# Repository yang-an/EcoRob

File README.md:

# EcoRob

Hier entsteht ein Repo für das Projekt AT im Wintersemester 2017/18 an der Hochschule München.

## Wozu kann das Repo verwendet werden?
* Software-Entwicklung
* Kommunikation (z.B. Abwesenheiten)
* Dokumentation (Wiki)
* ...

## Weitere Inhalte folgen!

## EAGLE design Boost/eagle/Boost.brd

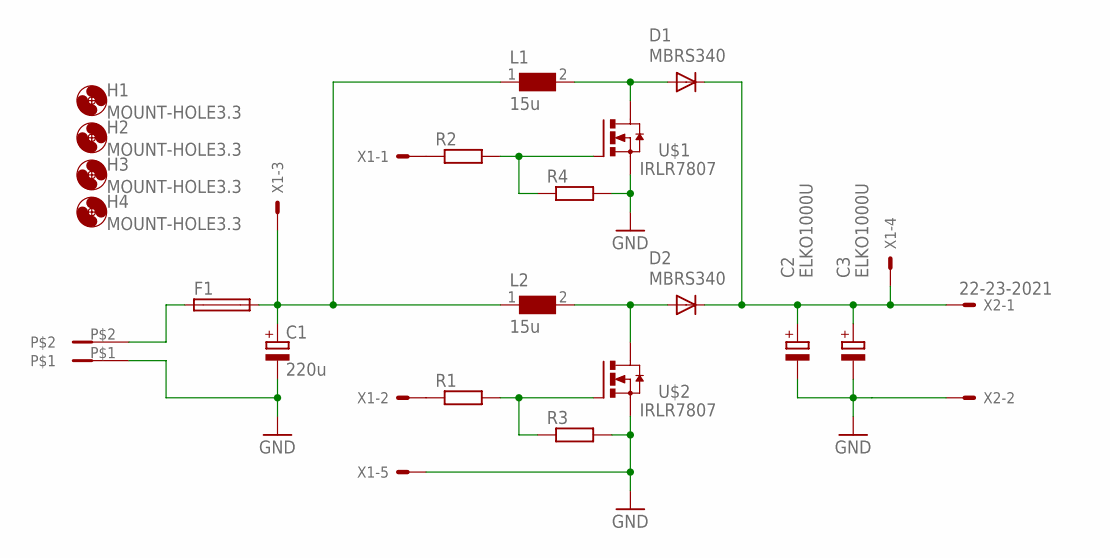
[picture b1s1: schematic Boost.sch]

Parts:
C1: 220u; PANASONIC_F
C2, C3: ELKO1000U; J16
D1, D2: MBRS340; SMC
F1: SH22,5
H1, H2, H3, H4: MOUNT-HOLE3.3; 3,3
L1, L2: 15u; WE-PD_1260/1245/1280/1210
R1, R2, R3, R4: R-EU_MELF0204W; MINI_MELF-0204W
U$1, U$2: IRLR7807; D-PAK
U$3: RIACON-2; RIACON2
X1: 22-23-2051
X2: 22-23-2021

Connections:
GND: C1.-, C2.-, C3.-, R3.2, R4.2, U$1.3 (S), U$2.3 (S), U$3.P$1, X1.5, X2.2
unnamed: F1.1, U$3.P$2
unnamed: R2.2, R4.1, U$1.1 (G)
unnamed: R1.1, X1.2
unnamed: R2.1, X1.1
unnamed: R1.2, R3.1, U$2.1 (G)
SW1: D1.A, L1.2, U$1.4 (D)
SW2: D2.A, L2.2, U$2.4 (D)
UIN: C1.+, F1.2, L1.1, L2.1, X1.3
UOUT: C2.+, C3.+, D1.C, D2.C, X1.4, X2.1

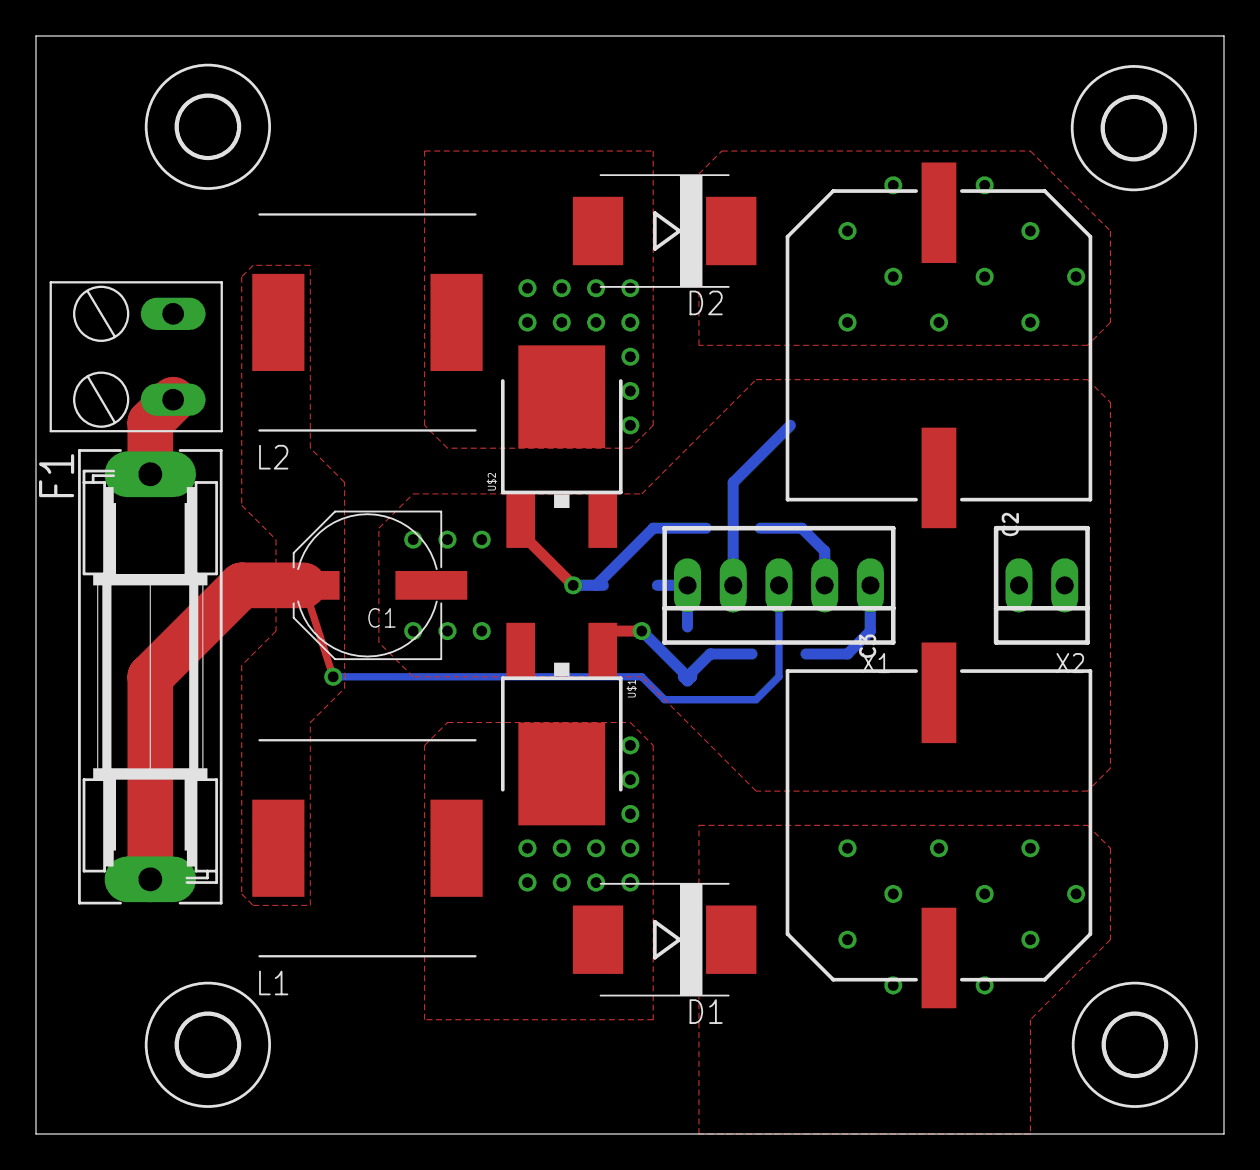
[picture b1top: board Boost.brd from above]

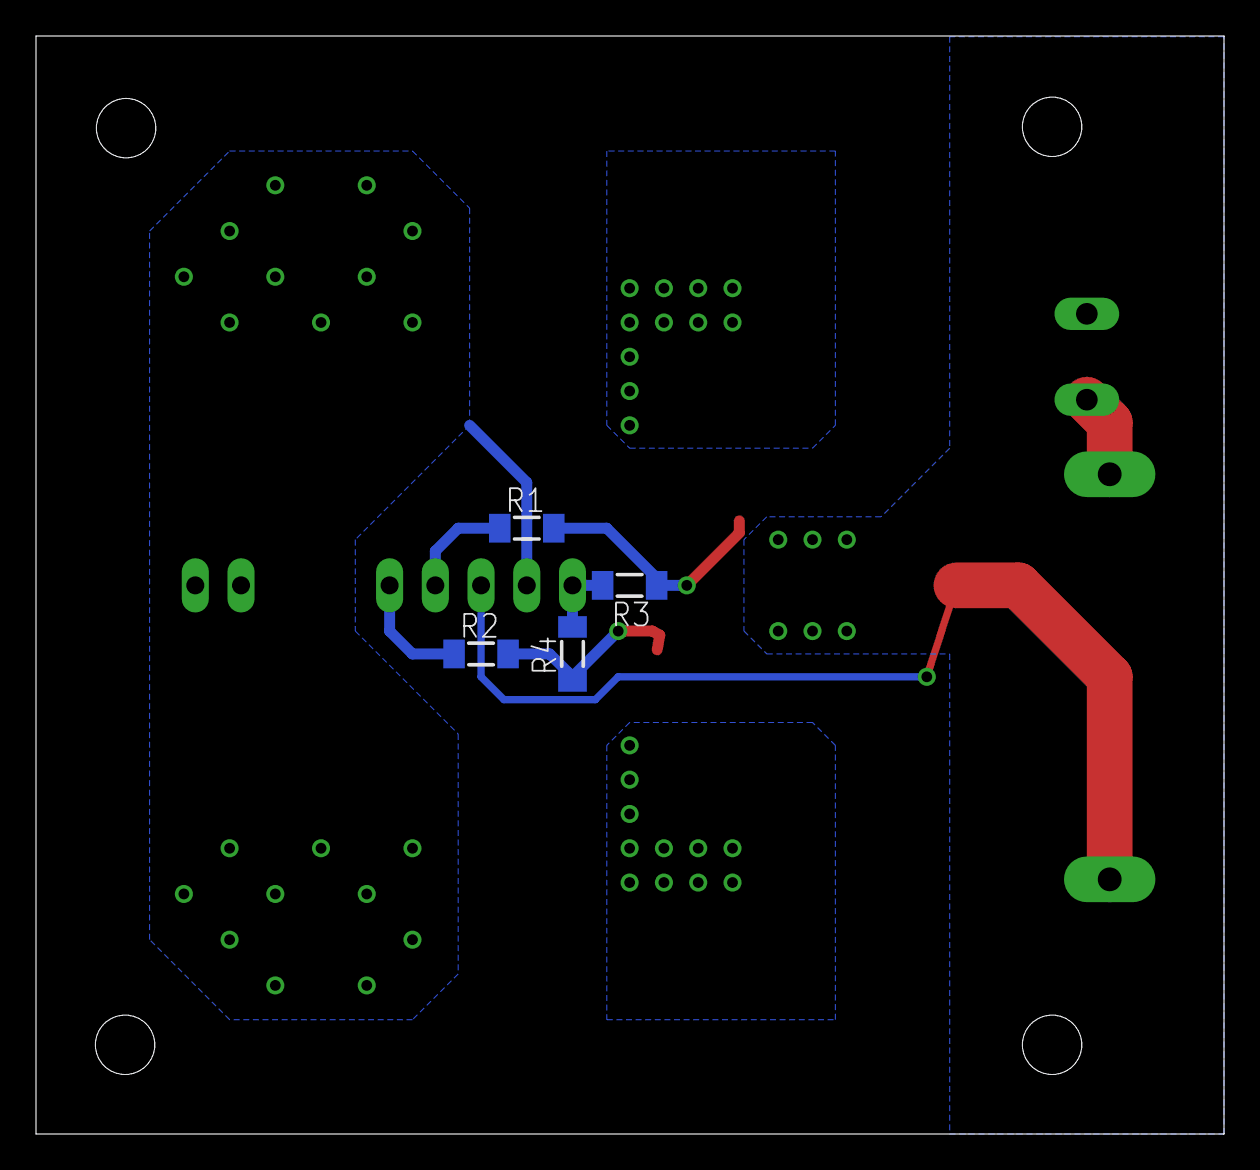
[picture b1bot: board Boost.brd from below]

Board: 2 copper layers, 66.0 x 61.0 mm, 21 parts (4 on the bottom side), 10 nets.

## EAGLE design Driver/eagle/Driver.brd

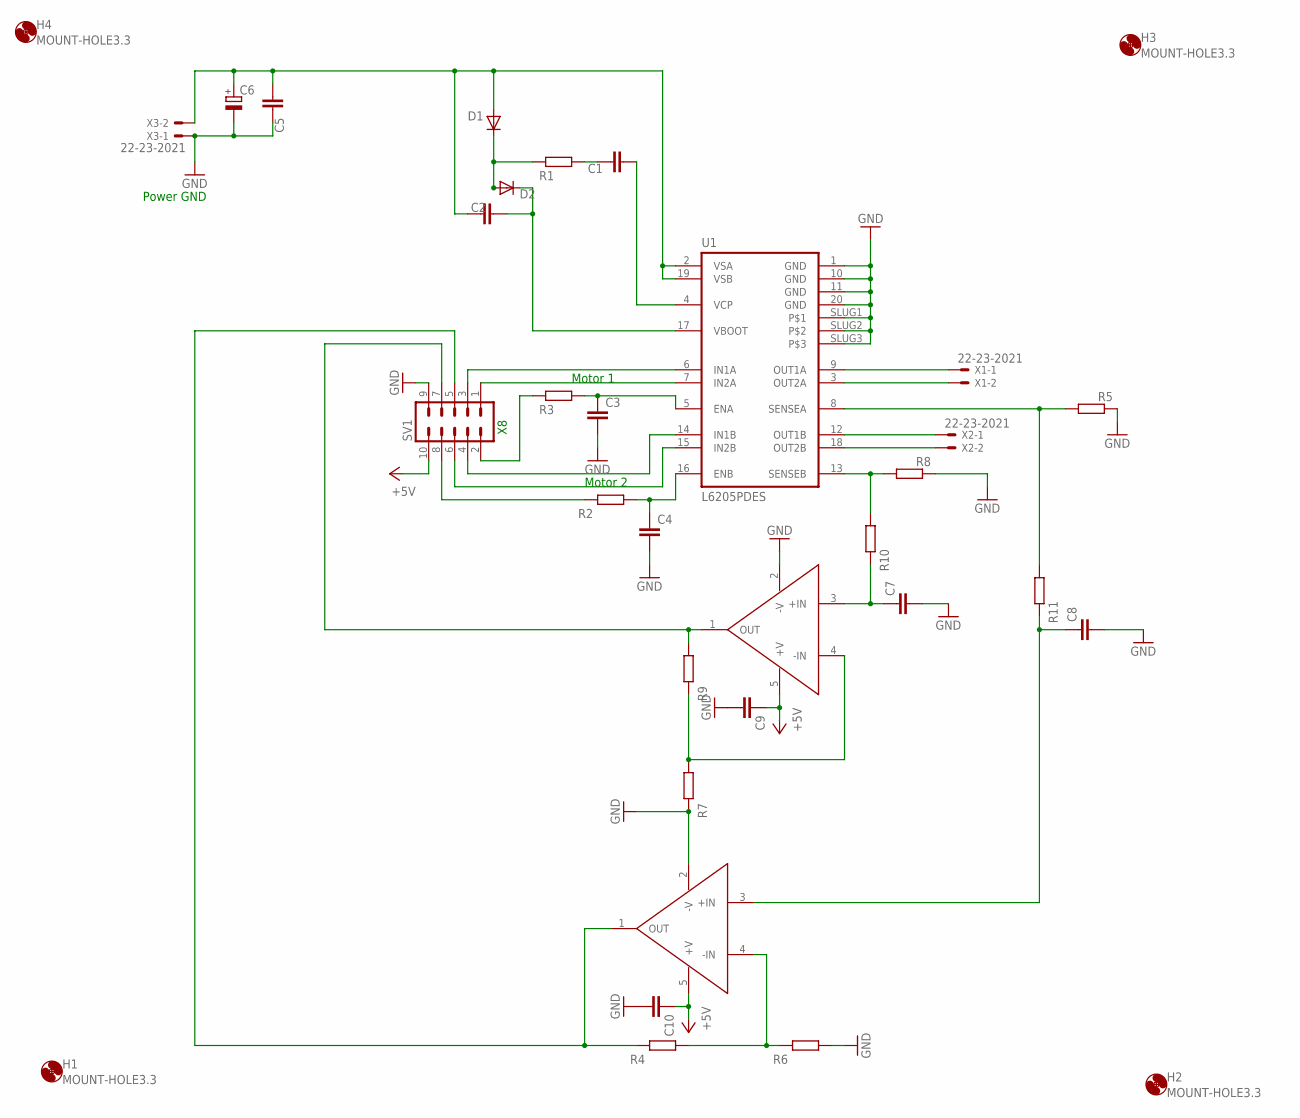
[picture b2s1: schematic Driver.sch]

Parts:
C1, C2, C5: C-EUC0805K; C0805K
C3, C4, C7, C8, C9, C10: C-EUC0805; C0805
C6: CPOL-EUE; PANASONIC_E
D1, D2: DIODE-MINIMELF; MINIMELF
H1, H2, H3, H4: MOUNT-HOLE3.3; 3,3
R1, R2, R3, R4, R6, R7, R9, R10, R11: R-EU_MELF0204W; MINI_MELF-0204W
R5, R8: R-EU_R2512W; R2512W
SV1: ML10
U1: L6205PDES; SO20POWER2
U$2, U$3: LM7301; SOT23-5
X1, X2, X3: 22-23-2021

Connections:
+5V: C9.1, C10.1, SV1.10, U$2.5 (+V), U$3.5 (+V)
GND: C3.2, C4.2, C5.1, C6.-, C7.2, C8.2, C9.2, C10.2, R5.1, R6.2, R7.1, R8.1, SV1.9, U1.1 (GND), U1.10 (GND), U1.11 (GND), U1.20 (GND), U1.SLUG1, U1.SLUG2, U1.SLUG3, U$2.2 (-V), U$3.2 (-V), X3.1
unnamed: C2.1, C5.2, C6.+, D1.A, U1.2 (VSA), U1.19 (VSB), X3.2
unnamed: D1.C, D2.A, R1.1
unnamed: C1.1, R1.2
unnamed: C1.2, U1.4 (VCP)
unnamed: C2.2, D2.C, U1.17 (VBOOT)
unnamed: SV1.3, U1.6 (IN1A)
unnamed: R3.1, SV1.2
unnamed: SV1.6, U1.15 (IN2B)
unnamed: C3.1, R3.2, U1.5 (ENA)
unnamed: SV1.4, U1.14 (IN1B)
unnamed: R2.1, SV1.8
unnamed: SV1.1, U1.7 (IN2A)
unnamed: R8.2, R10.2, U1.13 (SENSEB)
unnamed: C7.1, R10.1, U$3.3 (+IN)
unnamed: C4.1, R2.2, U1.16 (ENB)
unnamed: C8.1, R11.1, U$2.3 (+IN)
unnamed: R4.1, SV1.5, U$2.1 (OUT)
unnamed: R4.2, R6.1, U$2.4 (-IN)
unnamed: R5.2, R11.2, U1.8 (SENSEA)
unnamed: U1.18 (OUT2B), X2.2
unnamed: U1.12 (OUT1B), X2.1
unnamed: U1.3 (OUT2A), X1.2
unnamed: U1.9 (OUT1A), X1.1
unnamed: R9.2, SV1.7, U$3.1 (OUT)
unnamed: R7.2, R9.1, U$3.4 (-IN)

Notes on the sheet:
Motor 1
Motor 2
Power GND

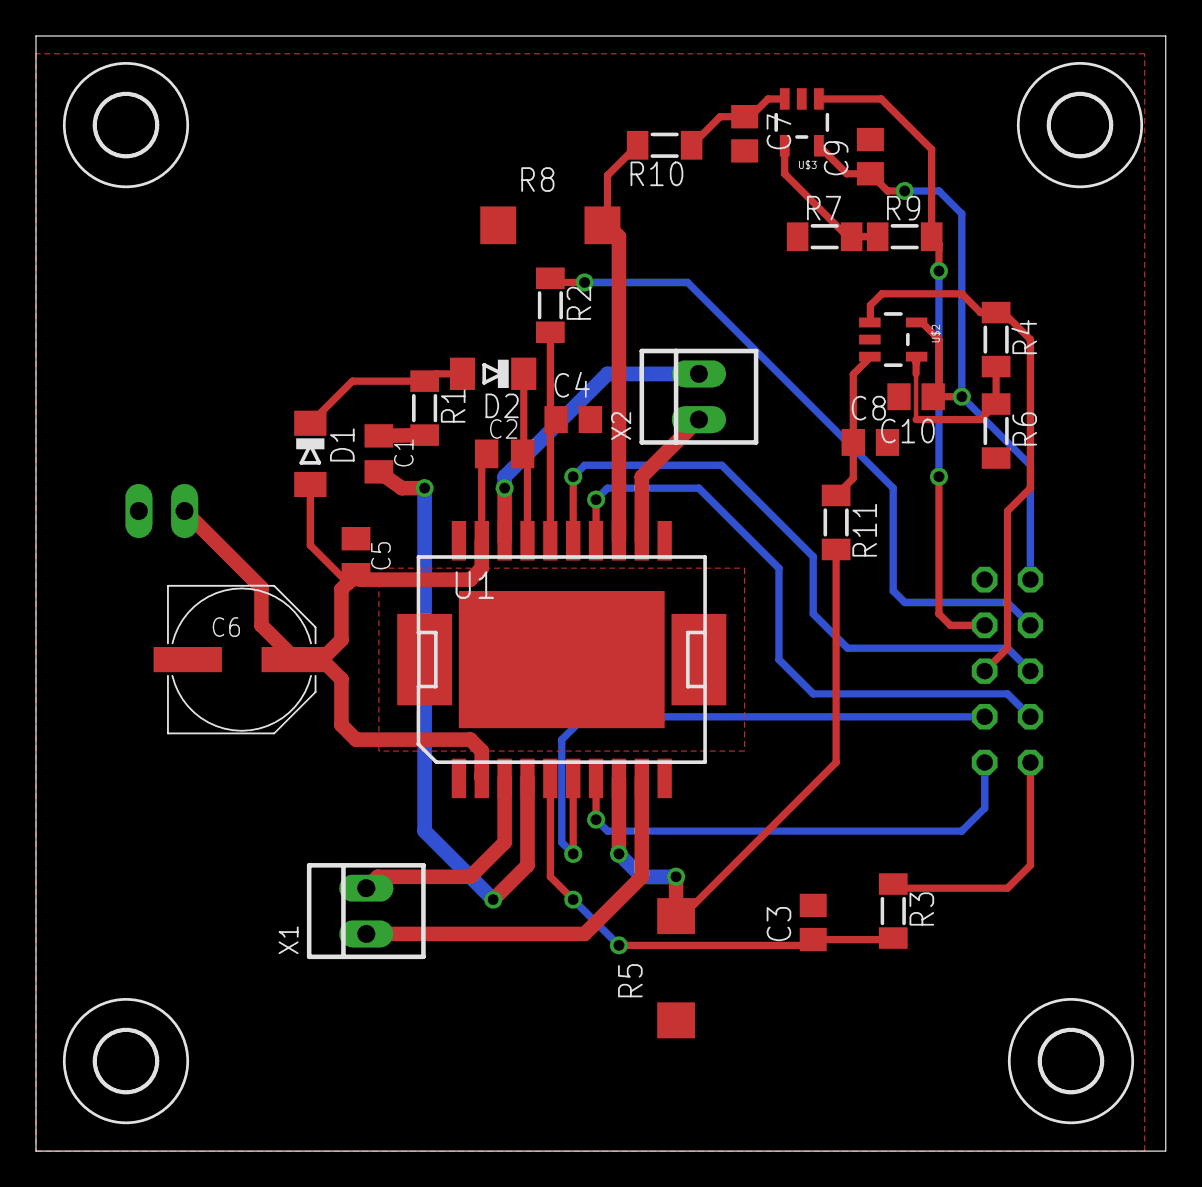
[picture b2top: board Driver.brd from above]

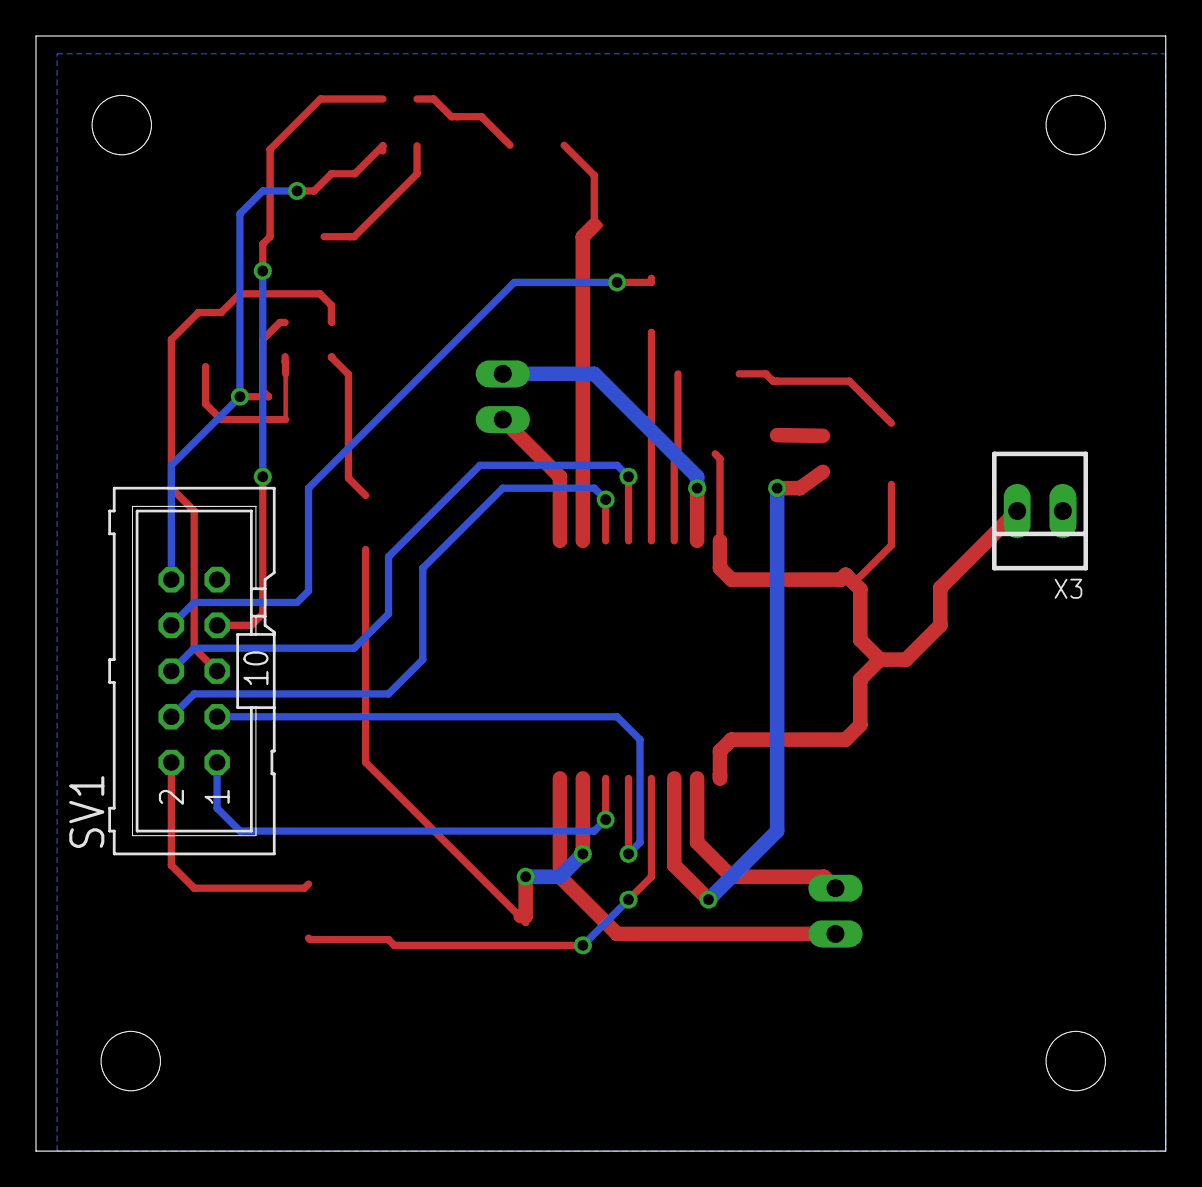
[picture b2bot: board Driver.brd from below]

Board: 2 copper layers, 62.8 x 62.0 mm, 34 parts (2 on the bottom side), 27 nets.

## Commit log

2017-10-12 add documents
2017-10-12 moved files
2017-10-18 move 'EcoRob.ino' to 'sensor_test'
2017-10-18 added first simulation of boost converter
2017-10-19 Erweiterung des Tutorial-Codes
2017-10-19 add boost conv pwm, documentation
2017-10-19 added .gitignore to ignore all eagle backup files
2017-10-19 added eagle project
2017-10-26 edit Pflichtenheft
2017-10-26 Aufbau einer Code-Struktur.
2017-10-26 updated boost converter layout
2017-11-01 added motor driver schematic and layout
2017-11-02 add icons
2017-11-02 monochrome icons
2017-11-02 added logo to boost converter pcb
2017-11-02 Diverese Änderungen und Erweiterungen.
2017-11-02 added globale defines and variables
2017-11-02 restructure code into modules
2017-11-02 added adc module
2017-11-02 move file
2017-11-05 update driver layout
2017-11-09 branch commit
2017-11-09 Updated driver schematic
2017-11-09 added files for pcb production
2017-11-09 fix adc trigger
2017-11-09 distance logging
2017-11-16 implemented boost controller
2017-11-16 test and verification
2017-12-07 updated boost controller
2017-12-07 add functions for cornering
2017-12-07 cleanup
2017-12-14 changed y from int16_t to int32_t to prevent overflow
2017-12-14 WIP commit
2017-12-14 change to fast PWM
2017-12-14 einfacher abstandsregler
2017-12-14 tweaks
2017-12-21 update pflichtenheft
2017-12-21 boost: change resistor values
2017-12-21 add booster documentation
2017-12-21 doku
2017-12-21 improved controller
2018-01-09 WIP motion control doc
2018-01-10 rename 'Motion Control' to 'Fahrstrategie'
2018-01-10 add simulation to boost converter documentation
2018-01-11 finalize documentation
    dummy
